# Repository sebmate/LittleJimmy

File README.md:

# LittleJimmy Crowbar Protection Circuit

## Introduction

LittleJimmy is a small crowbar circuit for Arduino-like development boards aiming to protect against a failing AMS1117 5.0V linear voltage regulator when the board is powered over VIN. 

Typically, these development boards use an "AMS1117" 5V voltage regulator of questionable quality (see [this](https://goughlui.com/2021/03/27/note-linear-regulator-woes-when-is-an-ams1117-not-an-ams1117) interesting blog post). This regulator may fail with a full or partial internal short and pass the input voltage (VIN) to the rest of the circuit. This may kill the microcontroller and all other components connected to the 5V rail.

Please note that real Arduino boards use high-quality linear voltage regulators. For these, there is no need to use the circuit presented here -- another good reason to buy the real Arduinos! The circuit is also not needed if the development board is powered via USB.

(In case you're wondering: The name "LittleJimmy" comes from the fact that in Britain and Australia a crowbar is also called a "jimmy". :smiley: )

## Licensing

The information and files in this repository are provided under the [CERN-OHL-S v2](cern_ohl_s_v2.txt) open source license (please click [here](https://ohwr.org/project/cernohl/wikis/Documents/CERN-OHL-version-2) for details).

## Implementation

The LittleJimmy board implements a "crowbar circuit" (see [this](https://circuitdigest.com/electronic-circuits/crowbar-circuit-diagram) link for an excellent description). In case the linear regulator fails, a Zener diode trips the thyristor and creates a full short on the 5V rail (hence the name "crowbar"), which then blows a fuse that protects the development board.

The LittleJimmy board has two connectors, one with 3 pins and one with 4 pins. The 3-pin connector can be used for the "MEGA 2560 PRO" board, the 4-pin connector with "Uno" or "Mega 2560" compatible development boards.

The board can accommodate two optional tantalum capacitors (C1 and C2) in case the "AMS1117" is to be replaced with another "1117"-type regulator from a renowned manufacturer (e.g. LM1117 by Texas Instruments or TS1117 by Taiwan Semiconductor), purchased from a reputable electronics distributor.

When using a 5.1 V Zener diode, the circuit should trip at about 5.5V, according to my tests. Note that not all 5.1 V Zener diodes behave the same. The "BZX 85C5V1", for example, trips the circuit at 4.5 V. This may need some experimentation. I therefore suggest to mount the diode in a way it can be easily replaced. Unfortunately I do not have a model number for the one I'm currently using. I hope to be able to provide details in the near future. Feedback is welcome!

**Important:** Note that it is necessary to protect VIN of the development board with a fuse. Its value must be high enough to not blow during normal operation, but lower than the allowed current of the thyristor (0.8A). Depending on the application, a 0.1A fuse might be a good choice.

## Testing the Circuit

To test the crowbar circuit, connect it to a laboratory power supply set to 3 V with a current limit of 50 mA. The circuit should draw (almost) no current and the power supply should be in constant voltage (CV) mode. Increase the voltage slowly. When it exceeds the Zener diode voltage, the thyristor should trip and produce a short circuit, and the power supply should go into constant current (CC) mode. Note that the circuit may not trip exactly at the Zener diode voltage (see above).

## Parts Lists

A list for the German electronics distributor Reichelt can be accessed directly via this link: [https://www.reichelt.de/my/2052760](https://www.reichelt.de/my/2052760). This list may contain alternative parts that are not essential. The list should therefore not be ordered blindly. Please note that I am not affiliated with Reichelt and am only providing this list for your convenience. The parts may be available from other vendors at a lower price.

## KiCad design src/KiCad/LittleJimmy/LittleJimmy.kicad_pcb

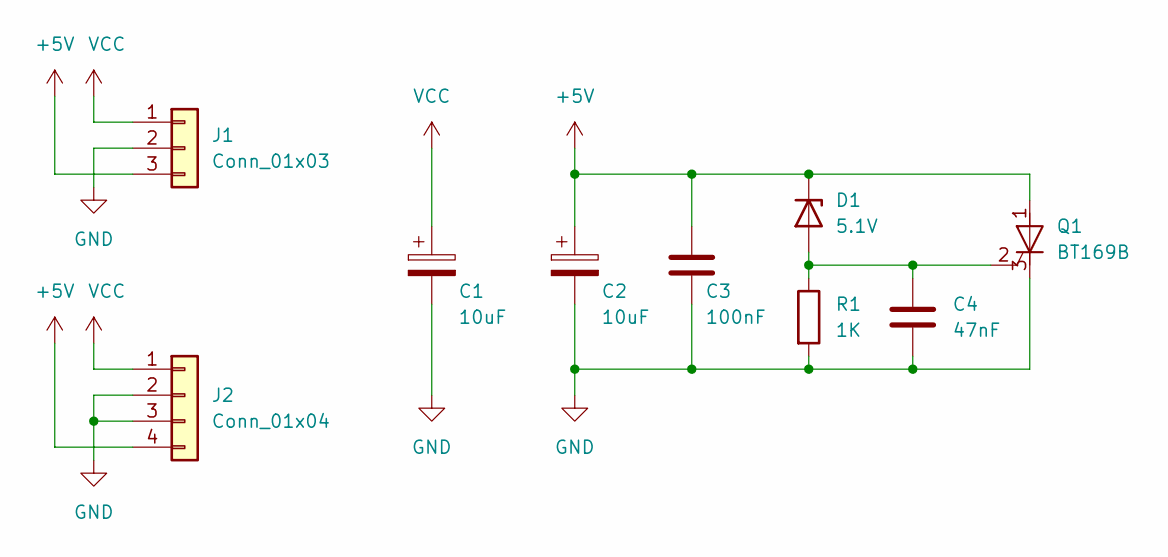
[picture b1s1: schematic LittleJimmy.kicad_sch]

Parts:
C1, C2: 10uF; CP_Radial_D5.0mm_P2.50mm
C3: 100nF; C_Rect_L7.0mm_W2.5mm_P5.00mm
C4: 47nF; C_Rect_L7.0mm_W2.5mm_P5.00mm
D1: 5.1V; D_DO-41_SOD81_P10.16mm_Horizontal
J1: Conn_01x03; PinHeader_1x03_P2.54mm_Vertical
J2: Conn_01x04; PinHeader_1x04_P2.54mm_Vertical
Q1: BT169B; TO-92L_Inline_Wide
R1: 1K; R_Axial_DIN0207_L6.3mm_D2.5mm_P10.16mm_Horizontal

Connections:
+5V: C2.1, C3.1, D1.1 (K), J1.3, J2.4, Q1.1 (A)
GND: C1.2, C2.2, C3.2, C4.2, J1.2, J2.2, J2.3, Q1.3 (K), R1.2
unnamed: C4.1, D1.2 (A), Q1.2 (G), R1.1
VCC: C1.1, J1.1, J2.1

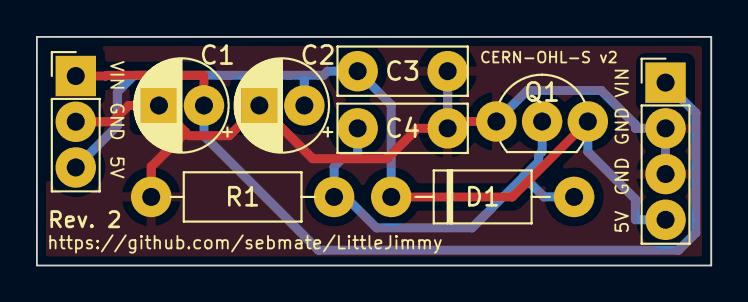
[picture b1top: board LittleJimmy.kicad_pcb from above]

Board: 2 copper layers, 37.5 x 12.7 mm, 9 parts (0 on the bottom side), 4 nets.

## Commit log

2023-05-13 Add files
2023-08-03 Update to Version 2
2023-08-14 Update to Version 2
    Version 2 fixes the following issues:
    - Wrong orientation of the BT169B thyristor
    - Wrong orientation of the connectors
2023-08-14 Update image
    Reduce file size
